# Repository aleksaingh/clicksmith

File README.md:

# Clicksmith
Clicksmith is a 3x3 macropad and it uses Custom HID via adafruit_hid firmware

I mostly built it because I just want a macropad laying around for macros and etc, that was my inspiration

## Challenges
For my challenges, I didn’t use Fusion 360 or KiCad at all before. In KiCad I got the hang of it pretty quick, but for Fusion 360 not so much.
I googled so much and I personally think that it's a stupid piece of software, but I'm pretty proud of my self and my HackPad. The most difficult part for me was probably designing the case because as I mentioned before Fusion 360 is a stupid piece of software.

## Specifications
BOM: 
- 9x Cherry MX Switches
- 2x SK6812 MINI Leds
- 1x XIAO RP2040
- 9x Blank DSA Keycaps
- 4x M3x16 Bolt
- 4x M3 Heatset

Others:
- Custom HID firmware
- ClicksmithTop.step (This is the plate)
- ClicksmithBottom.step

## Images
Schematic

PCB

Case

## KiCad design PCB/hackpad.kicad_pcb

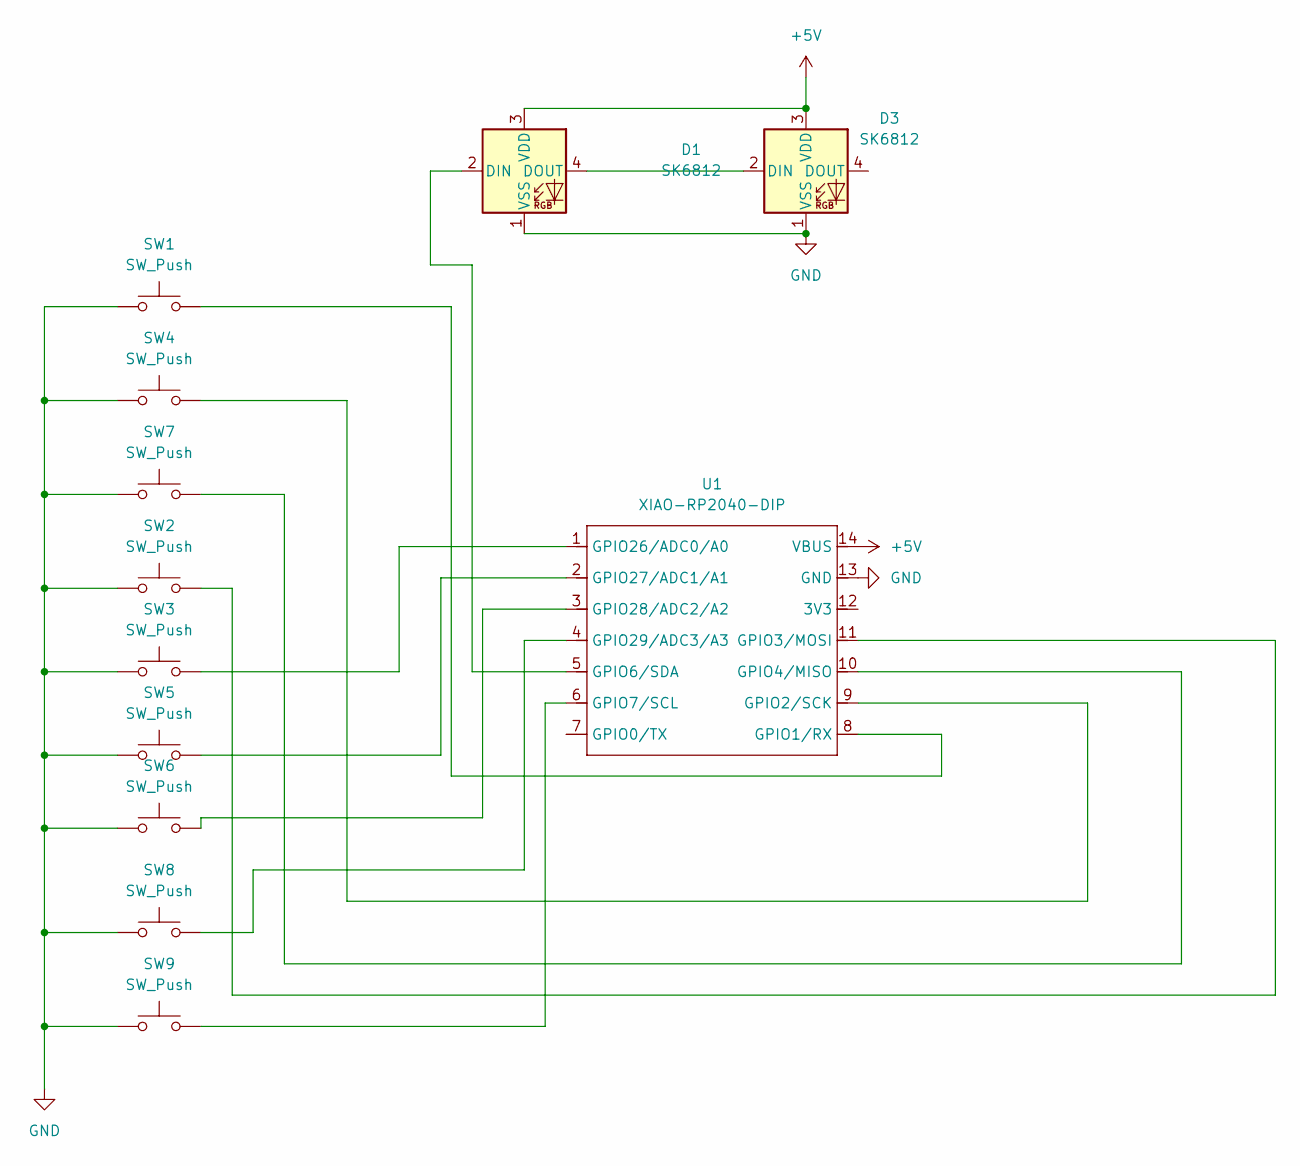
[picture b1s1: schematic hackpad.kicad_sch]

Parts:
D1, D3: SK6812; LED_SK6812MINI_PLCC4_3.5x3.5mm_P1.75mm
SW1, SW2, SW3, SW4, SW5, SW6, SW7, SW8, SW9: SW_Push; SW_Cherry_MX_1.00u_PCB
U1: XIAO-RP2040-DIP

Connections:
+5V: D1.3 (VDD), D3.3 (VDD), U1.14 (VBUS)
GND: D1.1 (VSS), D3.1 (VSS), SW1.1, SW2.1, SW3.1, SW4.1, SW5.1, SW6.1, SW7.1, SW8.1, SW9.1, U1.13 (GND)
unnamed: D1.2 (DIN), U1.5 (GPIO6/SDA)
unnamed: D1.4 (DOUT), D3.2 (DIN)
unnamed: SW1.2, U1.8 (GPIO1/RX)
unnamed: SW4.2, U1.9 (GPIO2/SCK)
unnamed: SW2.2, U1.11 (GPIO3/MOSI)
unnamed: SW7.2, U1.10 (GPIO4/MISO)
unnamed: SW9.2, U1.6 (GPIO7/SCL)
unnamed: SW3.2, U1.1 (GPIO26/ADC0/A0)
unnamed: SW5.2, U1.2 (GPIO27/ADC1/A1)
unnamed: SW6.2, U1.3 (GPIO28/ADC2/A2)
unnamed: SW8.2, U1.4 (GPIO29/ADC3/A3)

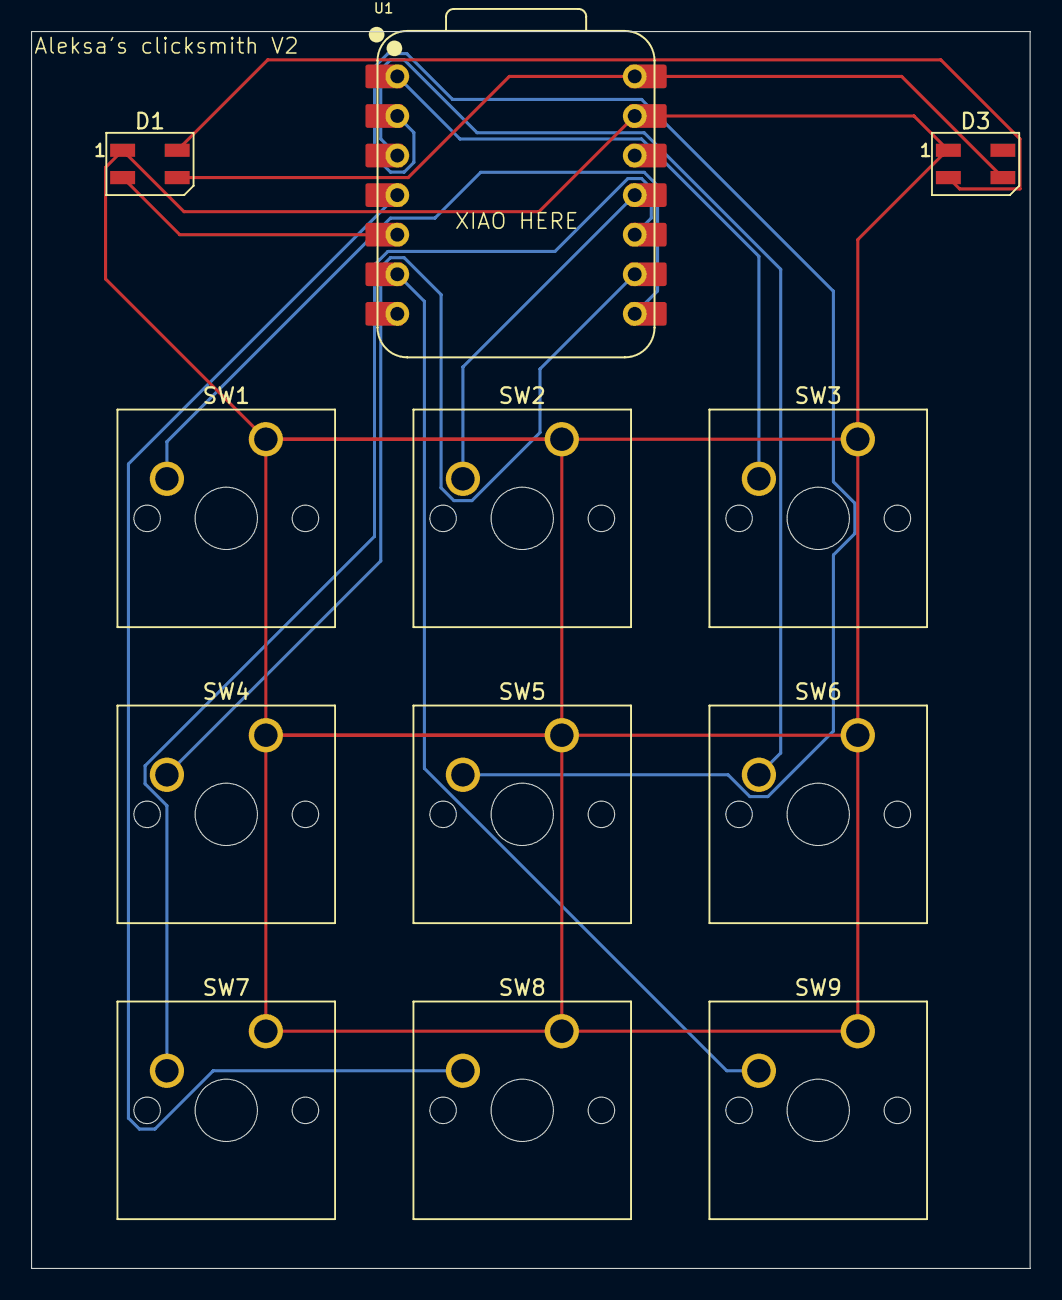
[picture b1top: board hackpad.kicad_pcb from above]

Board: 2 copper layers, 64.1 x 79.4 mm, 12 parts (0 on the bottom side), 13 nets.

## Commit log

2026-01-18 Create PCB
2026-01-18 Delete
2026-01-18 Create e
2026-01-18 Create 1
2026-01-20 Add README
2026-01-20 Fix formatting and update image references in README
2026-04-03 Adding firmware to its own folder
2026-04-03 Move firmware files into Firmware subfolder
